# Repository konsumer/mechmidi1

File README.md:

This is a [RP2040-Zero](https://www.waveshare.com/rp2040-zero.htm) mechanical keyboard I designed to be a MIDI controller/sequencer and/or macro-keypad. It's made to be highly configurable & easy to modify.

> [!CAUTION]
> After assembling, I think the keys are a tiny bit too close together (spacing left/right should be doubled) and I think the RP2040 needs a board-cutout to make it lay flush. You can solder it as it is, but it makes it much harder, because it has a gap between the boards. I am currently reworking the design in Kicad, and might attempt to test another iteration, if I do another run. I talk about these issues [in this video](https://www.youtube.com/watch?v=3DC8_nlmCxc) (as well as give a general tour)

## Features

- 20-key keypad with MX-style switches
- OLED 128x64 display
- 2 rotary encoders (each with a button)
- 20 RGB LEDs
- i2c port for adding more stuff (for example I might make a dongle for bluetooth or USB midi/keyboard/mouse/gamepad host)
- old-school MIDI in/out
- I used pi 2040, but you can use any chip, with a little modification
- designed to be easy to reflow-solder with a toaster oven, if you are manufacturing/assembling yourself
- Fully programmable with [CircuitPython](https://circuitpython.org/)
- Use [KMK](https://github.com/KMKfw/kmk_firmware) for a more keyboard-focused python-programmable firmware
- Use MIDI-focused firmware over USB, or with oldschool MIDI-out, that does sequencing
- translate USB MIDI to oldschool MIDI (no USB host, but it can interact with computer)
- pattern/song/track sequencer for sequencing drums
- pattern/song/track sequencer for sequencing notes
- arpeggio sequencer

## build/install

- order PCB & parts. Feel free to use whatever cheaper parts you can find. It pays to look around, especially with the OLED and LED chips. The key-switches are also totally up to you, but I recommend something clear, so the light shines through better. You will also need keycaps (again, clear or matte white looks nice)
- if you want to use easyeda & [jlcpcb](https://jlcpcb.com/) (it's very cheap & easy) you can disable any parts you don't need/want in BOM, and it will leave them out. For example, I didn't use the keys or 2040 they listed, I used my own (and it ended up better, I think.)
- solder components on board. [this](https://learn.sparkfun.com/tutorials/how-to-solder-castellated-mounting-holes/all) was helpful for the RP2040-Zero. Flux really helps, and a cheap USB microscope, if you have one. Basically, I fluxed it up, put a pointy tipped iron in slot, then added a lil solder, for each pin. If you are soldering the other parts, it should be easier with a toaster/hotplate, since all the parts are on one side.
- if you want classic MIDI, connect a board, like [this](https://www.amazon.com/ubld-itTM-Breakout-Board-Multi-Voltage/dp/B0BYMC926Z) to "expansion port" on board. I did this as a seperate board because I had a MIDI breakout-board laying around and I wanted it all to fit on a very small main-board. Another trick is sometimes the MIDI ports are included with other features on the board. For example [this](https://shop.m5stack.com/products/midi-unit-with-din-connector-sam2695) has MIDI DIN IN/OUT, as well as TRS MIDI ports, and has a full sound-engine built in (entire General Midi of 128 decent-sounding instruments.) Even if you don't want the sounds, the MIDI connections alone are useful, but with sounds, it makes the device even cooler!
- [install circuitpython](https://circuitpython.org/board/waveshare_rp2040_zero/) and any [libs](https://circuitpython.org/libraries) you need to "circuitpython" disk, in lib dir. You can skip this if you want arduino or some other firmware, but circuitpython is recommended initially, to test things, easily. For me, the whole circuitpython bundle was too big, so just copy [firmware](firmware). My code.py is meant to test each part initially (so you can make sure hardware/software is setup right.) I also included a lib dir, so you shouldn;t need anything else, to get started.
- move sequencer.py to code.py, and reboot, and you should have a complete device.

### expansion & hardware

At the top-left of board, there is an expansion port for MIDI/serial/i2c/power.

```
[GND] (3V3) (TX) (RX) (SCL) (SDA)
```

Use this to hook up classic midi daughter-board, or any other i2c/serial thing you want.

If you need to access these pins in code or want to expand the board, here is how they are hooked up to the RP2040-Zero:

- `VCC` (3.3V) and `GND` are power. I did not expose `5V`, but you could add it to expansion-port, or you can just add a bodge-wire to chip-pin or one of the through-holes on board, if you need that. IO is best at `3.3V` for this chip, so I wanted to keep it all "easy to stay safe"
- `LED` is a neopixel-line (has 20 RGB LEDs on it, but you can add many more.) Again, a bodge-wire will be needed to add more pixels to this line, but it's fairly easy to solder one on, if you need that.
- `COL(X)`/`ROW(X)` are the keyboard-matrix
- `ROT(X)A`/`ROT(X)B`/`ROT(X)S` are the rotary-encoders (`S` is the push-down switch)
- `SDA`/`SCL` is i2c. You can add up to 127 devices to this bus (each has it's own address, and they share wires) but OLED takes up 1 slot
- `RX`/`TX` is serial or classic MIDI (with a little circuit)

### cost

You can definitely find these cheaper, if you look around. Although it's cheaper than any nice MIDI controller/sequencer/synth I found, that did what I want, super-cheap was not really a goal for me, with this project. It could be done differently, and much cheaper, I just wanted everything to work just like this, and be pretty quick/easy to assemble (it's a gift for a young-person, with not too much soldering experience.)

If you do it all my way, the per-unit cost is about $40, not including addons or whatever. A [nice midi & sound addon](https://shop.m5stack.com/products/midi-unit-with-din-connector-sam2695) is another $15.

- board with assembly - a bit cheaper in bulk, with assembly. I ordered 10, at $16 each (including shipping) and it has most of the parts on the board (no RP2040 or keys.) In much larger quantites, the price goes way down, and you can shop around for cheapest board (I went with easiest.) I can sell you a pre-populated board for $16 (not including shipping to you) until I run out. I currently have 5 of these on-hand. You can also get the price down by etching/assembling yourself, and just ordering parts (in bulk) but some of the parts are a bit tricky to solder by hand (a toaster would work better for the LEDs and diodes.) $16 seems pretty cheap to me, and the hardest soldering is done, and it's mostly all built, but some nice & fun soldering is left.
- RP2040-Zero - I bought [3 for $20](https://www.amazon.com/gp/product/B0BZ8D4CJM/?th) and got it the next day, but they are definitely way cheaper elsewhere (check aliexpress/etc) if you are willing to wait for shipping, especially if you are buying them in bulk (they are very useful for all kinds of things.)
- mech key switches - I used [these nice ones](https://www.amazon.com/gp/product/B0CDW74TX3), $20 for 45 (enough for 2 devices) but you can find these much cheaper.
- keycaps - I used [these](https://www.amazon.com/gp/product/B0CQ2XD4WT). $12 for 20, or $31 for 100. XDA is less "scuplted" than Cherry, but either will work fine.

To build 10, it's about $260 ($26 per unit):

- boards $160 - go cheaper by making your own, or printing/assembling more at a time. Assembly is not very expensive compared to the PCB, I have found, so it might be worth it to add $2 per-unit and save yourself some time/effort.
- key switches $84 - you can definitely find these cheaper on aliexpress
- [10 2040s](https://www.aliexpress.us/item/3256806922860079.html) $15
- order some super-cheap keycaps that will work for you. clear is best, but white will work fine, too. If you are ok with lettering on them, you can reuse a super-cheap macropad-set.

You could get this even cheaper with greater bulk-quantities, and shopping around, though.

### ideas for cheaper

- Use membrane-keys (silicone buttons over PCB traces) instead of mech-keys
- drop LEDs, or use single-color
- drop OLED
- drop rotary-encoders
- try to get all parts on single-side (for cheaper/easier-to-make-at-home PCB)

## Modify

This thing is meant to be hacked!

### hardware

- Install [EasyEDA](https://easyeda.com/)
- move things in schematice however you want, or add/remove anyhting you like. Make sure to update PCB (alt-I.) The 2040 is maxed-out for GPIO, but the layout should be simple enough to modify (unroute all, then do your business with nets like `COL0`, `ROW0`, etc, then auto-route.) I recommend replacing the chip wityh somerthing bigger if you want to do ther stuff (see [picoadk](https://www.tindie.com/products/datanoisetv/picoadk-audio-development-kit-raspberry-rp2040/) for a nice 2040 firmware for larger pico, with sound-generatin in mind!)

### software

If you want to change how the software works, I have created a [simple lib](firmware/midimech1.py) to interact with the existing hardware in [CircuitPython](https://circuitpython.org/). See how I use it in [sequencer.py](firmware/sequencer.py). If you change the hardware, you will probly need to also modify these.

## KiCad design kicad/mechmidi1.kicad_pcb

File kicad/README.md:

This is Kicad source for the hardware.

You should install these 2 libs, if you want to edit things:

- [ScottoKeebs](https://github.com/joe-scotto/scottokeebs/tree/main/Extras/ScottoKicad)
- [RP2040-Zero-Kicad](https://github.com/CountParadox/RP2040-Zero-Kicad)

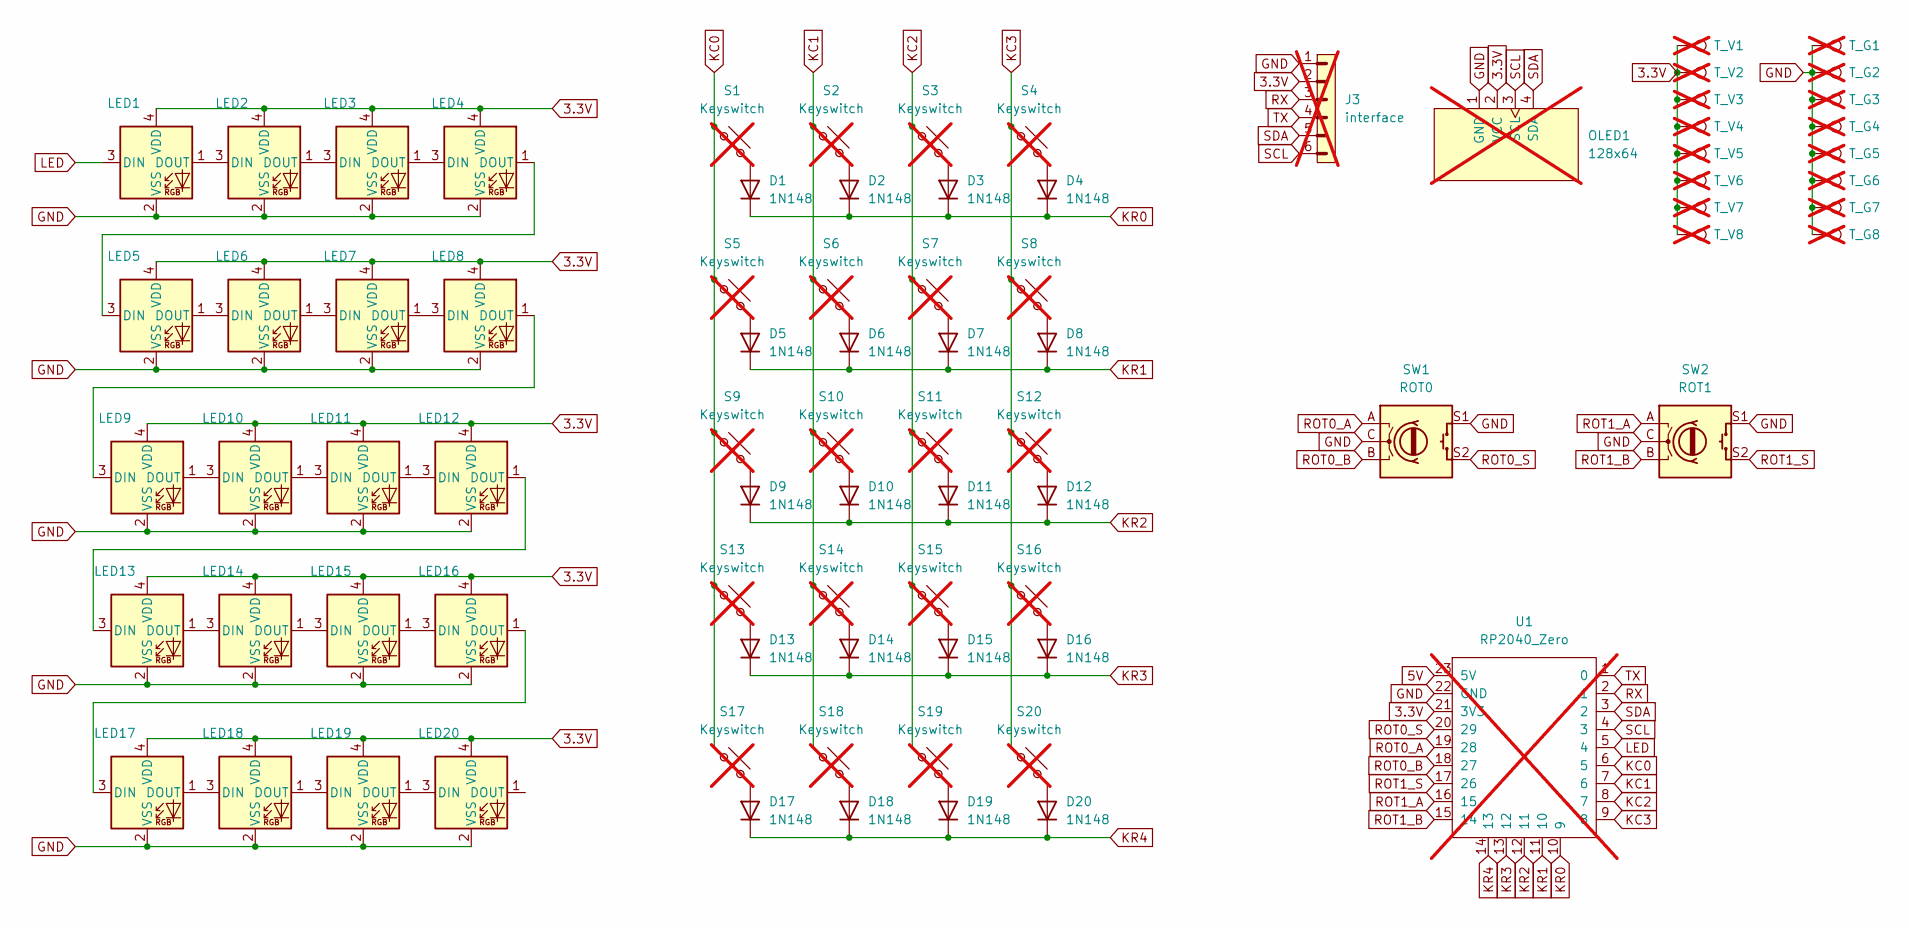
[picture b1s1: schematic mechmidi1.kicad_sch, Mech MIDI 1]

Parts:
D1, D2, D3, D4, D5, D6, D7, D8, D9, D10, D11, D12, D13, D14, D15, D16, D17, D18, D19, D20: 1N148; D_SOD-123
J3: interface; PinHeader_1x06_P2.54mm_Vertical; not fitted
LED1, LED2, LED3, LED4, LED5, LED6, LED7, LED8, LED9, LED10, LED11, LED12, LED13, LED14, LED15, LED16, LED17, LED18, LED19, LED20: WS2812B-2020; LED_WS2812B-2020_PLCC4_2.0x2.0mm
OLED1: 128x64; OLED_128x64; not fitted
S1, S2, S3, S4, S5, S6, S7, S8, S9, S10, S11, S12, S13, S14, S15, S16, S17, S18, S19, S20: Keyswitch; MX_PCB_1.00u; not fitted
SW1: ROT0; RotaryEncoder_Alps_EC11E-Switch_Vertical_H20mm
SW2: ROT1; RotaryEncoder_Alps_EC11E-Switch_Vertical_H20mm
T_G1, T_G2, T_G3, T_G4, T_G5, T_G6, T_G7, T_G8: TestPoint; Pin_D0.7mm_L6.5mm_W1.8mm_FlatFork; not fitted
T_V1, T_V2, T_V3, T_V4, T_V5, T_V6, T_V7, T_V8: TestPoint; Pin_D0.7mm_L6.5mm_W1.8mm_FlatFork; not fitted
U1: RP2040_Zero; not fitted

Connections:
3.3V: J3.2, LED1.4 (VDD), LED2.4 (VDD), LED3.4 (VDD), LED4.4 (VDD), LED5.4 (VDD), LED6.4 (VDD), LED7.4 (VDD), LED8.4 (VDD), LED9.4 (VDD), LED10.4 (VDD), LED11.4 (VDD), LED12.4 (VDD), LED13.4 (VDD), LED14.4 (VDD), LED15.4 (VDD), LED16.4 (VDD), LED17.4 (VDD), LED18.4 (VDD), LED19.4 (VDD), LED20.4 (VDD), OLED1.2 (VCC), T_V1.1, T_V2.1, T_V3.1, T_V4.1, T_V5.1, T_V6.1, T_V7.1, T_V8.1, U1.21 (3V3)
5V: U1.23 (5V)
GND: J3.1, LED1.2 (VSS), LED2.2 (VSS), LED3.2 (VSS), LED4.2 (VSS), LED5.2 (VSS), LED6.2 (VSS), LED7.2 (VSS), LED8.2 (VSS), LED9.2 (VSS), LED10.2 (VSS), LED11.2 (VSS), LED12.2 (VSS), LED13.2 (VSS), LED14.2 (VSS), LED15.2 (VSS), LED16.2 (VSS), LED17.2 (VSS), LED18.2 (VSS), LED19.2 (VSS), LED20.2 (VSS), OLED1.1 (GND), SW1.C, SW1.S1, SW2.C, SW2.S1, T_G1.1, T_G2.1, T_G3.1, T_G4.1, T_G5.1, T_G6.1, T_G7.1, T_G8.1, U1.22 (GND)
KC0: S1.1, S5.1, S9.1, S13.1, S17.1, U1.6 (5)
KC1: S2.1, S6.1, S10.1, S14.1, S18.1, U1.7 (6)
KC2: S3.1, S7.1, S11.1, S15.1, S19.1, U1.8 (7)
KC3: S4.1, S8.1, S12.1, S16.1, S20.1, U1.9 (8)
KR0: D1.1 (K), D2.1 (K), D3.1 (K), D4.1 (K), U1.10 (9)
KR1: D5.1 (K), D6.1 (K), D7.1 (K), D8.1 (K), U1.11 (10)
KR2: D9.1 (K), D10.1 (K), D11.1 (K), D12.1 (K), U1.12 (11)
KR3: D13.1 (K), D14.1 (K), D15.1 (K), D16.1 (K), U1.13 (12)
KR4: D17.1 (K), D18.1 (K), D19.1 (K), D20.1 (K), U1.14 (13)
LED: LED1.3 (DIN), U1.5 (4)
unnamed: D1.2 (A), S1.2
unnamed: D2.2 (A), S2.2
unnamed: D3.2 (A), S3.2
unnamed: D4.2 (A), S4.2
unnamed: D5.2 (A), S5.2
unnamed: D6.2 (A), S6.2
unnamed: D7.2 (A), S7.2
unnamed: D8.2 (A), S8.2
unnamed: D9.2 (A), S9.2
unnamed: D10.2 (A), S10.2
unnamed: D11.2 (A), S11.2
unnamed: D12.2 (A), S12.2
unnamed: D13.2 (A), S13.2
unnamed: D14.2 (A), S14.2
unnamed: D15.2 (A), S15.2
unnamed: D16.2 (A), S16.2
unnamed: D17.2 (A), S17.2
unnamed: D18.2 (A), S18.2
unnamed: D19.2 (A), S19.2
unnamed: D20.2 (A), S20.2
unnamed: LED1.1 (DOUT), LED2.3 (DIN)
unnamed: LED2.1 (DOUT), LED3.3 (DIN)
unnamed: LED3.1 (DOUT), LED4.3 (DIN)
unnamed: LED4.1 (DOUT), LED5.3 (DIN)
unnamed: LED5.1 (DOUT), LED6.3 (DIN)
unnamed: LED6.1 (DOUT), LED7.3 (DIN)
unnamed: LED7.1 (DOUT), LED8.3 (DIN)
unnamed: LED8.1 (DOUT), LED9.3 (DIN)
unnamed: LED9.1 (DOUT), LED10.3 (DIN)
unnamed: LED10.1 (DOUT), LED11.3 (DIN)
unnamed: LED11.1 (DOUT), LED12.3 (DIN)
unnamed: LED12.1 (DOUT), LED13.3 (DIN)
unnamed: LED13.1 (DOUT), LED14.3 (DIN)
unnamed: LED14.1 (DOUT), LED15.3 (DIN)
unnamed: LED15.1 (DOUT), LED16.3 (DIN)
unnamed: LED16.1 (DOUT), LED17.3 (DIN)
unnamed: LED17.1 (DOUT), LED18.3 (DIN)
unnamed: LED18.1 (DOUT), LED19.3 (DIN)
unnamed: LED19.1 (DOUT), LED20.3 (DIN)
ROT0_A: SW1.A, U1.19 (28)
ROT0_B: SW1.B, U1.18 (27)
ROT0_S: SW1.S2, U1.20 (29)
ROT1_A: SW2.A, U1.16 (15)
ROT1_B: SW2.B, U1.15 (14)
ROT1_S: SW2.S2, U1.17 (26)
RX: J3.3, U1.2 (1)
SCL: J3.6, OLED1.3 (SCL), U1.4 (3)
SDA: J3.5, OLED1.4 (SDA), U1.3 (2)
TX: J3.4, U1.1 (0)

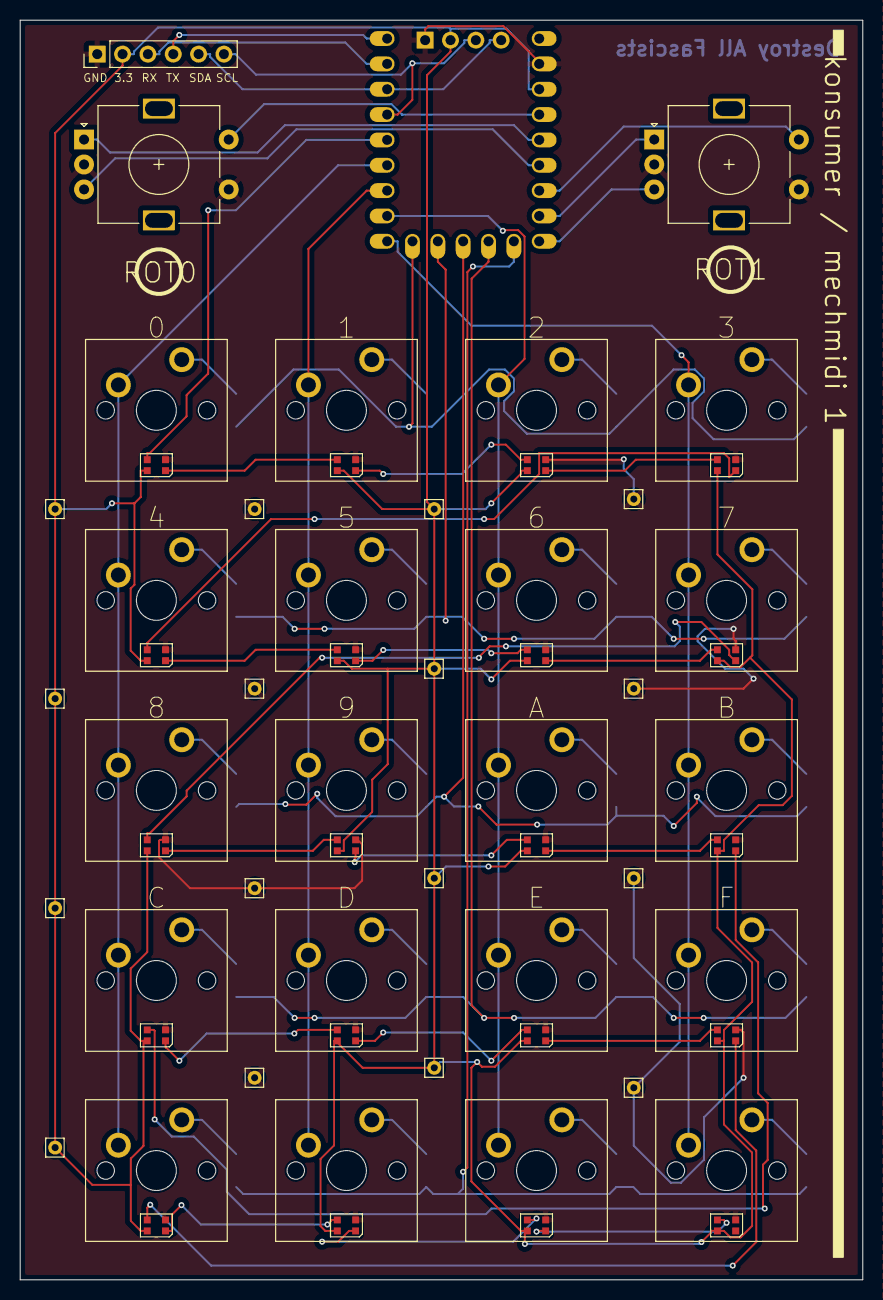
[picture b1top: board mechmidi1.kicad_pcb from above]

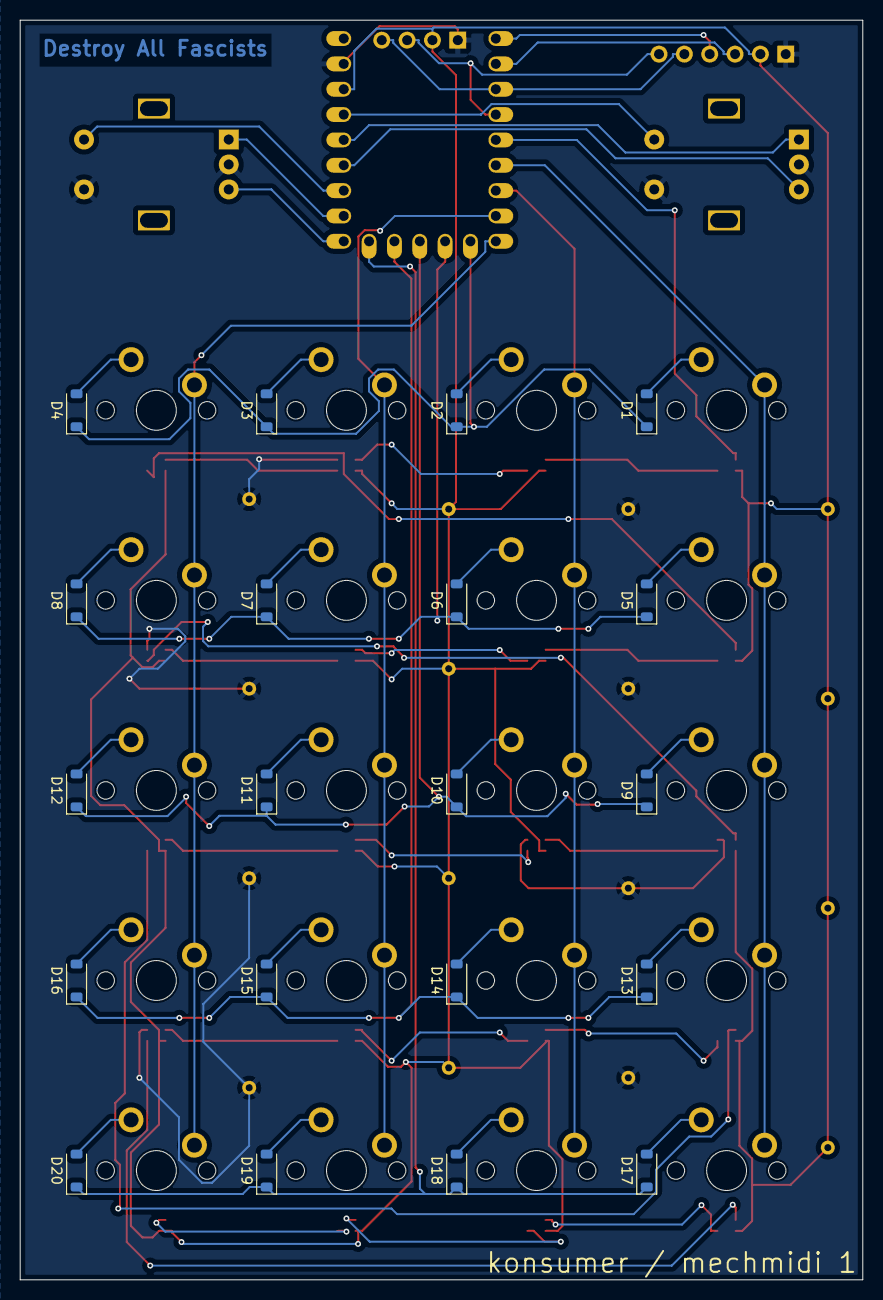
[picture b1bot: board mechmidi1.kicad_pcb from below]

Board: 2 copper layers, 84.4 x 126.2 mm, 81 parts (21 on the bottom side), 61 nets.

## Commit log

2025-02-05 more images
2025-02-05 typo
2025-02-05 images
2025-02-06 move all the things off main board
2025-02-08 cleanup wayward files
2025-02-08 working on new PCB ideas
2025-02-08 easyeda
2025-02-28 schematic image
2025-02-28 wrong expansion port
2025-03-01 More pin explanations
2025-03-02 more complete firmware
2025-03-02 reworked firmware a bit
2025-03-02 improve firmware and test
2025-03-02 font not needed with displayio
2025-03-03 nicer demo menu
2025-03-03 logo in demo menu
2025-03-03 design warnings
2025-03-05 sam/midi demos
2025-03-05 note about sam
2025-03-05 reset rotary on load
2025-03-09 working on sequencer
2025-03-10 moving back to kicad
